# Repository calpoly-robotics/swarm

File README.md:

swarm
=====

The base will, every so often, poll every address on the bus to see who is there.
We may have it restrict to a smaller number of addresses for increased efficiency
The base will then, device by device, ask them if they have any data to offload.

TODO:
	MX25L25635EZNI-12G
	UART with base station
	base station test code
	Buzzer
	Ledtask
		blink specific led
		on for duration
	Battery task
		when voltage is <3.4V full sleep. wake every few minutes
		when voltage is <3.6V sleep. Wake every minute and be annoying
	Just ensure all hardware has code

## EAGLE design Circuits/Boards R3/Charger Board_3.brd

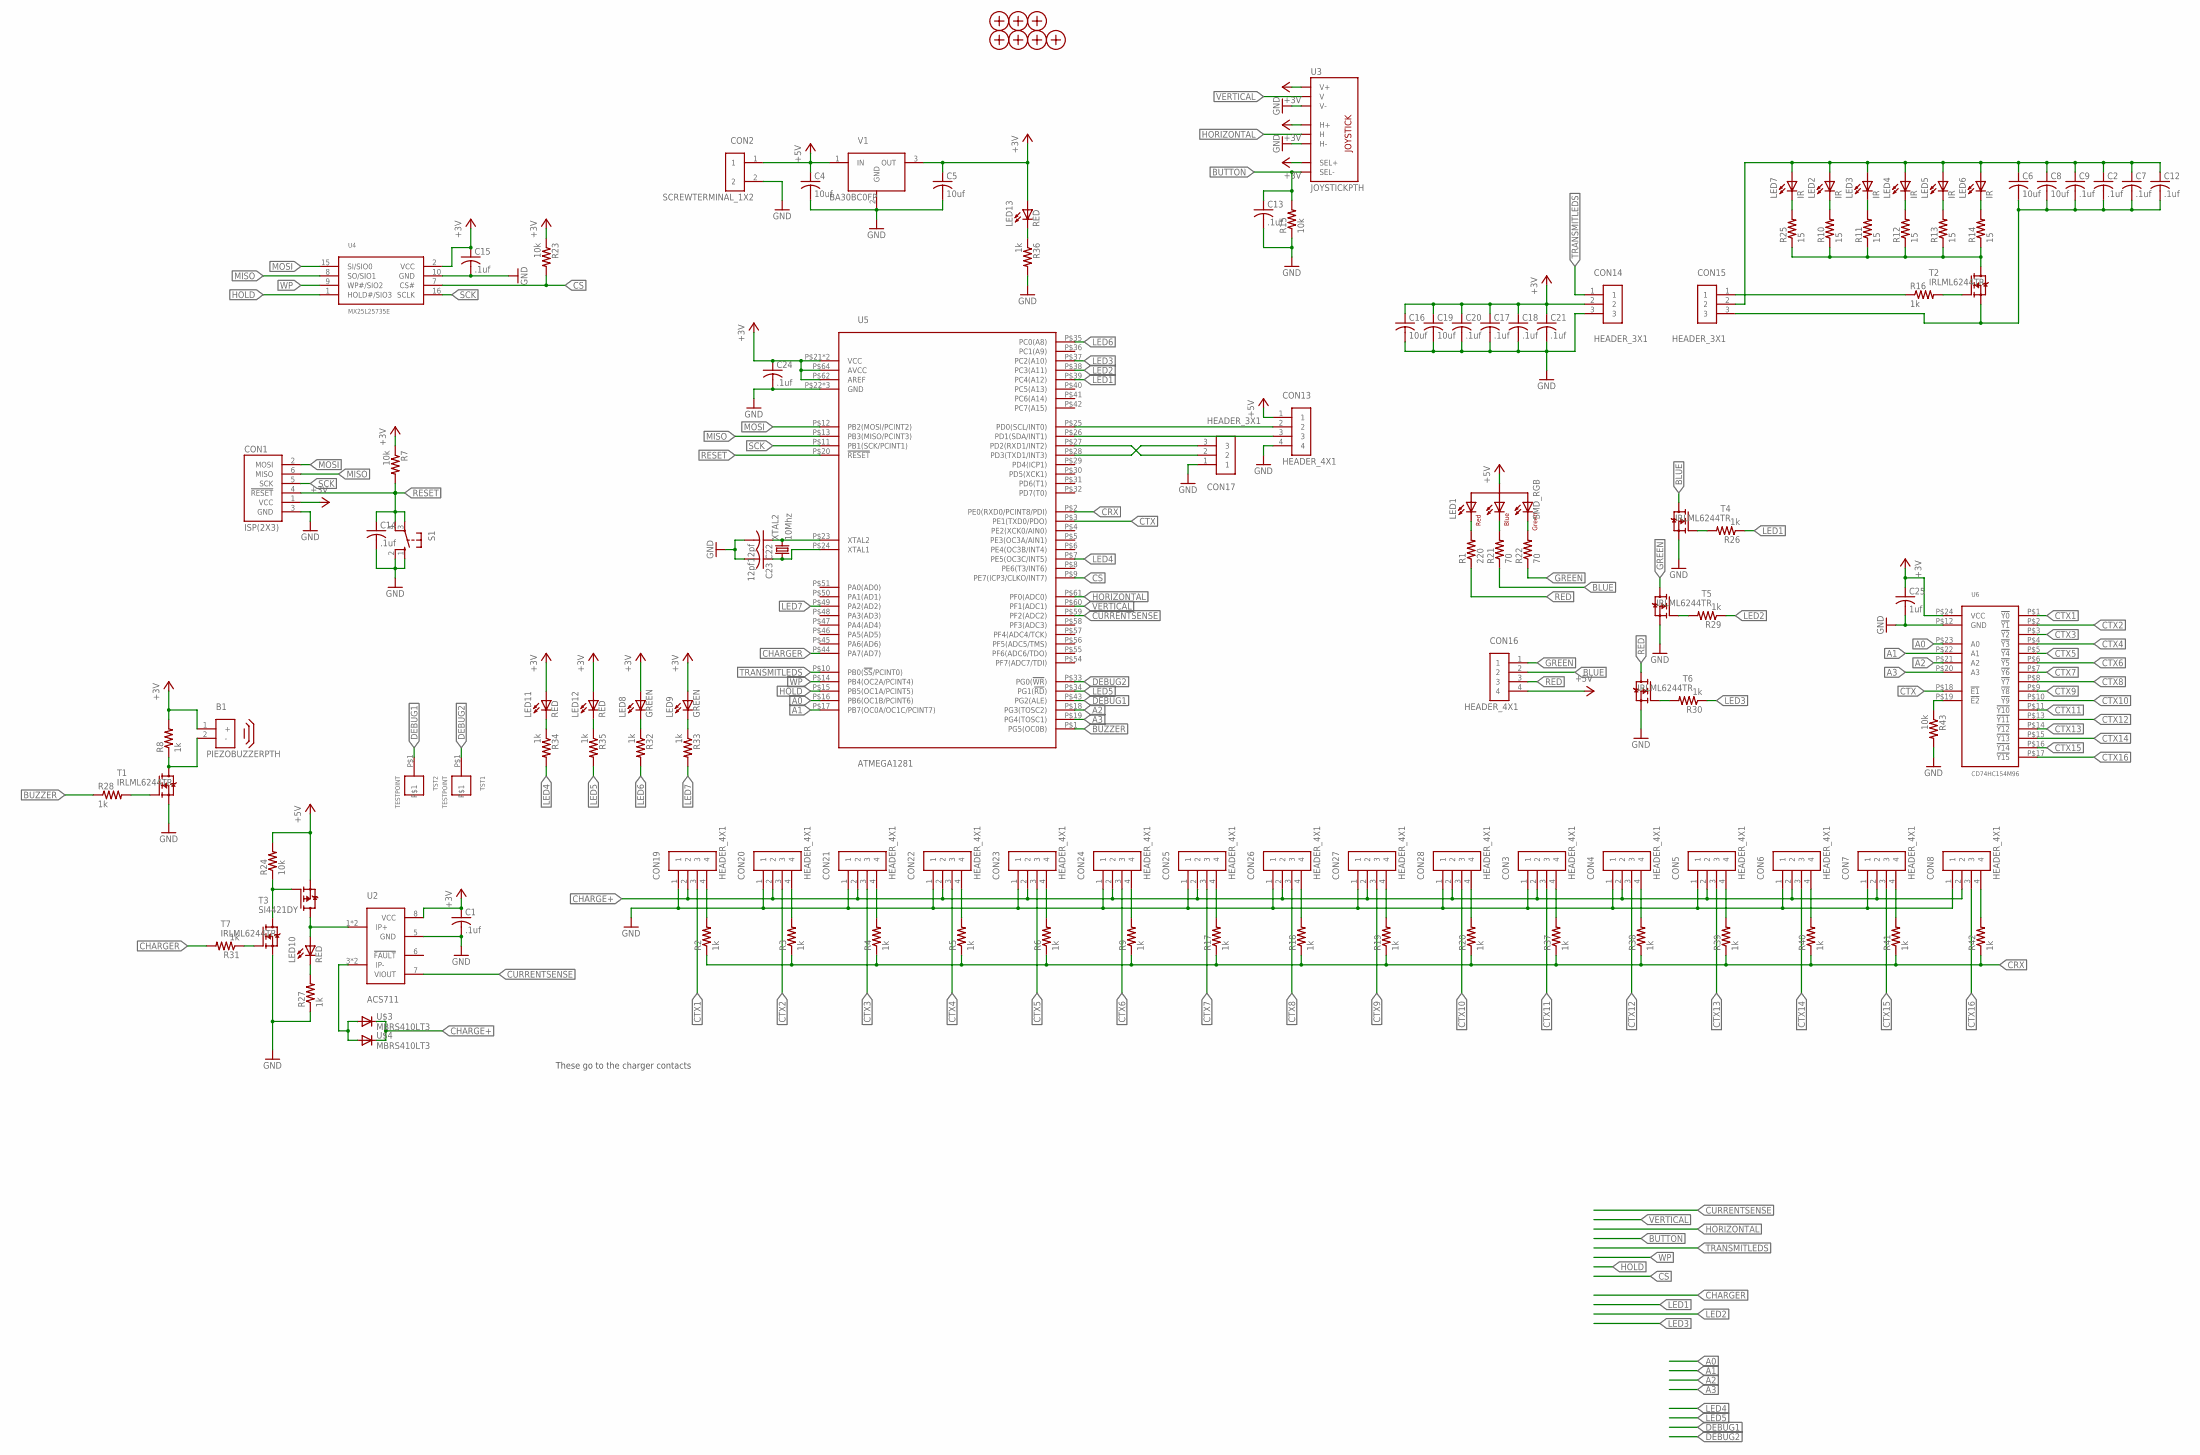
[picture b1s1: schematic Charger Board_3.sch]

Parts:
B1: PIEZOBUZZERPTH; PIEZOBUZZER
C1, C2, C7, C9, C12, C13, C14, C15, C17, C18, C20, C21, C24: .1uf; 0603
C4, C5, C6, C8, C16, C19: 10uf; 0805
C22, C23: 12pf; 0603
C25: 1uf; 0603
CON1: ISP(2X3); PINHEADER(2X3)
CON2: SCREWTERMINAL_1X2
CON3, CON4, CON5, CON6, CON7, CON8, CON13, CON16, CON19, CON20, CON21, CON22, CON23, CON24, CON25, CON26, CON27, CON28: HEADER_4X1; 4PINHEADER_.100"
CON14, CON15, CON17: HEADER_3X1; 3PINHEADER_.100"
H1, H2, H3, H4, H5, H6, H7: MOUNTINGHOLE
LED1: SMD_RGB; PLCC4
LED2, LED3, LED4, LED5, LED6, LED7: IR; 5MM_LED_RA
LED8, LED9: GREEN; LED0603
LED10, LED11, LED12, LED13: RED; LED0603
R1: 220; 0603
R2, R3, R4, R5, R6, R8, R9, R16, R17, R18, R19, R20, R26, R27, R28, R29, R30, R31, R32, R33, R34, R35, R36, R37, R38, R39, R40, R41, R42: 1k; 0603
R7, R15, R23, R24, R43: 10k; 0603
R10, R11, R12, R13, R14, R25: 15; 0603
R21, R22: 70; 0603
S1: 10-XX; B3F-10XX
T1, T2, T4, T5, T6, T7: IRLML6244TR; SOT23
T3: SI4421DY; S0-8
TST1, TST2: TESTPOINT
U2: ACS711; 8SOIC
U3: JOYSTICKPTH; JOYSTICK
U4: MX25L25735E; SOIC16R
U5: ATMEGA1281; TQFP64
U6: CD74HC154M96; 24SOIC
U$3, U$4: MBRS410LT3; SMD_DIODE
V1: BA30BC0FP; DPAK
XTAL2: 10Mhz; SMDXTAL

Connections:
+3V: B1.1 (+), C1.1, C5.1, C15.1, C16.1, C17.1, C18.1, C19.1, C20.1, C21.1, C24.1, C25.1, CON1.1 (VCC), CON14.2, LED8.2 (A), LED9.2 (A), LED11.2 (A), LED12.2 (A), LED13.2 (A), R7.1, R8.2, R23.1, U2.8 (VCC), U3.B1A (SEL+), U3.H1 (H+), U3.V1 (V+), U4.2 (VCC), U5.P$21 (VCC), U5.P$52 (VCC), U5.P$62 (AREF), U5.P$64 (AVCC), U6.P$24 (VCC), V1.3 (OUT)
+5V: C4.1, CON2.1, CON13.1, CON16.4, LED1.2 (COMMONANODE), R24.2, T3.1 (S), T3.2 (S), T3.3 (S), V1.1 (IN)
A0: U5.P$16 (PB6(OC1B/PCINT6)), U6.P$23 (A0)
A1: U5.P$17 (PB7(OC0A/OC1C/PCINT7)), U6.P$22 (A1)
A2: U5.P$18 (PG3(TOSC2)), U6.P$21 (A2)
A3: U5.P$19 (PG4(TOSC1)), U6.P$20 (A3)
BLUE: CON16.2, R21.1, T4.3 (D)
BUTTON: C13.1, R15.2, U3.B2A (SEL-)
BUZZER: R28.1, U5.P$1 (PG5(OC0B))
CHARGE+: CON3.2, CON4.2, CON5.2, CON6.2, CON7.2, CON8.2, CON19.2, CON20.2, CON21.2, CON22.2, CON23.2, CON24.2, CON25.2, CON26.2, CON27.2, CON28.2, U$3.2 (C), U$4.2 (C)
CHARGER: R31.2, U5.P$44 (PA7(AD7))
CRX: R2.1, R3.1, R4.1, R5.1, R6.1, R9.1, R17.1, R18.1, R19.1, R20.1, R37.1, R38.1, R39.1, R40.1, R41.1, R42.1, U5.P$2 (PE0(RXD0/PCINT8/PDI))
CS: R23.2, U4.7 (CS#), U5.P$9 (PE7(ICP3/CLKO/INT7))
CTX: U5.P$3 (PE1(TXD0/PDO)), U6.P$18 (!E1)
CTX1: CON19.3, U6.P$1 (!Y0)
CTX2: CON20.3, U6.P$2 (!Y1)
CTX3: CON21.3, U6.P$3 (!Y2)
CTX4: CON22.3, U6.P$4 (!Y3)
CTX5: CON23.3, U6.P$5 (!Y4)
CTX6: CON24.3, U6.P$6 (!Y5)
CTX7: CON25.3, U6.P$7 (!Y6)
CTX8: CON26.3, U6.P$8 (!Y7)
CTX9: CON27.3, U6.P$9 (!Y8)
CTX10: CON28.3, U6.P$10 (!Y9)
CTX11: CON3.3, U6.P$11 (!Y10)
CTX12: CON4.3, U6.P$13 (!Y11)
CTX13: CON5.3, U6.P$14 (!Y12)
CTX14: CON6.3, U6.P$15 (!Y13)
CTX15: CON7.3, U6.P$16 (!Y14)
CTX16: CON8.3, U6.P$17 (!Y15)
CURRENTSENSE: U2.7 (VIOUT), U5.P$59 (PF2(ADC2))
DEBUG1: TST2.P$1, U5.P$43 (PG2(ALE))
DEBUG2: TST1.P$1, U5.P$33 (PG0(!WR!))
GND: C1.2, C4.2, C5.2, C13.2, C14.2, C15.2, C16.2, C17.2, C18.2, C19.2, C20.2, C21.2, C22.2, C23.2, C24.2, C25.2, CON1.3 (GND), CON2.2, CON3.1, CON4.1, CON5.1, CON6.1, CON7.1, CON8.1, CON13.4, CON14.3, CON17.1, CON19.1, CON20.1, CON21.1, CON22.1, CON23.1, CON24.1, CON25.1, CON26.1, CON27.1, CON28.1, R15.1, R27.1, R36.2, R43.2, S1.1 (S), S1.2 (S1), T1.2 (S), T4.2 (S), T5.2 (S), T6.2 (S), T7.2 (S), U2.5 (GND), U3.H3 (H-), U3.V3 (V-), U4.10 (GND), U5.P$22 (GND), U5.P$53 (GND), U5.P$63 (GND), U6.P$12 (GND), V1.2 (GND)
GREEN: CON16.1, R22.1, T5.3 (D)
HOLD: U4.1 (HOLD#/SIO3), U5.P$15 (PB5(OC1A/PCINT5))
HORIZONTAL: U3.H2 (H), U5.P$61 (PF0(ADC0))
LED1: R26.1, U5.P$39 (PC4(A12))
LED2: R29.1, U5.P$38 (PC3(A11))
LED3: R30.1, U5.P$37 (PC2(A10))
LED4: R34.2, U5.P$7 (PE5(OC3C/INT5))
LED5: R35.2, U5.P$34 (PG1(!RD!))
LED6: R32.2, U5.P$35 (PC0(A8))
LED7: R33.2, U5.P$49 (PA2(AD2))
MISO: CON1.6 (MISO), U4.8 (SO/SIO1), U5.P$13 (PB3(MISO/PCINT3))
MOSI: CON1.2 (MOSI), U4.15 (SI/SIO0), U5.P$12 (PB2(MOSI/PCINT2))
unnamed: LED10.2 (A), T3.5 (D), T3.6 (D), T3.7 (D), T3.8 (D), U2.1 (IP+), U2.2 (IP+)
unnamed: CON15.1, R16.1
unnamed: C2.1, C6.1, C7.1, C8.1, C9.1, C12.1, CON15.2, LED2.1 (A), LED3.1 (A), LED4.1 (A), LED5.1 (A), LED6.1 (A), LED7.1 (A)
unnamed: C2.2, C6.2, C7.2, C8.2, C9.2, C12.2, CON15.3, T2.2 (S)
unnamed: LED7.2 (C), R25.2
unnamed: B1.2 (-), R8.1, T1.3 (D)
unnamed: R10.1, R11.1, R12.1, R13.1, R14.1, R25.1, T2.3 (D)
unnamed: R16.2, T2.1 (G)
unnamed: LED2.2 (C), R10.2
unnamed: LED3.2 (C), R11.2
unnamed: LED4.2 (C), R12.2
unnamed: LED5.2 (C), R13.2
unnamed: LED6.2 (C), R14.2
unnamed: R24.1, T3.4 (G), T7.3 (D)
unnamed: R31.1, T7.1 (G)
unnamed: LED10.1 (C), R27.2
unnamed: U2.3 (IP-), U2.4 (IP-), U$3.1 (A), U$4.1 (A)
unnamed: CON20.4, R3.2
unnamed: R28.2, T1.1 (G)
unnamed: CON19.4, R2.2
unnamed: CON21.4, R4.2
unnamed: CON22.4, R5.2
unnamed: CON23.4, R6.2
unnamed: CON24.4, R9.2
unnamed: CON25.4, R17.2
unnamed: CON26.4, R18.2
unnamed: CON27.4, R19.2
unnamed: CON28.4, R20.2
unnamed: R26.2, T4.1 (G)
unnamed: LED1.1 (REDCATHODE), R1.2
unnamed: LED1.3 (BLUECATHODE), R21.2
unnamed: LED1.4 (GREENCATHODE), R22.2
unnamed: R29.2, T5.1 (G)
unnamed: R30.2, T6.1 (G)
unnamed: LED8.1 (C), R32.1
unnamed: LED9.1 (C), R33.1
unnamed: LED11.1 (C), R34.1
unnamed: LED12.1 (C), R35.1
unnamed: LED13.1 (C), R36.1
unnamed: C22.1, U5.P$23 (XTAL2), XTAL2.2
unnamed: C23.1, U5.P$24 (XTAL1), XTAL2.1
unnamed: CON3.4, R37.2
unnamed: CON4.4, R38.2
unnamed: CON5.4, R39.2
unnamed: CON6.4, R40.2
unnamed: CON7.4, R41.2
unnamed: CON8.4, R42.2
unnamed: CON13.2, U5.P$25 (PD0(SCL/INT0))
unnamed: CON13.3, U5.P$26 (PD1(SDA/INT1))
unnamed: R43.1, U6.P$19 (!E2)
unnamed: CON17.2, U5.P$27 (PD2(RXD1/INT2))
unnamed: CON17.3, U5.P$28 (PD3(TXD1/INT3))
RED: CON16.3, R1.1, T6.3 (D)
RESET: C14.1, CON1.4 (!RESET), R7.2, S1.3, S1.4 (P1), U5.P$20 (!RESET!)
SCK: CON1.5 (SCK), U4.16 (SCLK), U5.P$11 (PB1(SCK/PCINT1))
TRANSMITLEDS: CON14.1, U5.P$10 (PB0(!SS!/PCINT0))
VERTICAL: U3.V2 (V), U5.P$60 (PF1(ADC1))
WP: U4.9 (WP#/SIO2), U5.P$14 (PB4(OC2A/PCINT4))

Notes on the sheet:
These go to the charger contacts

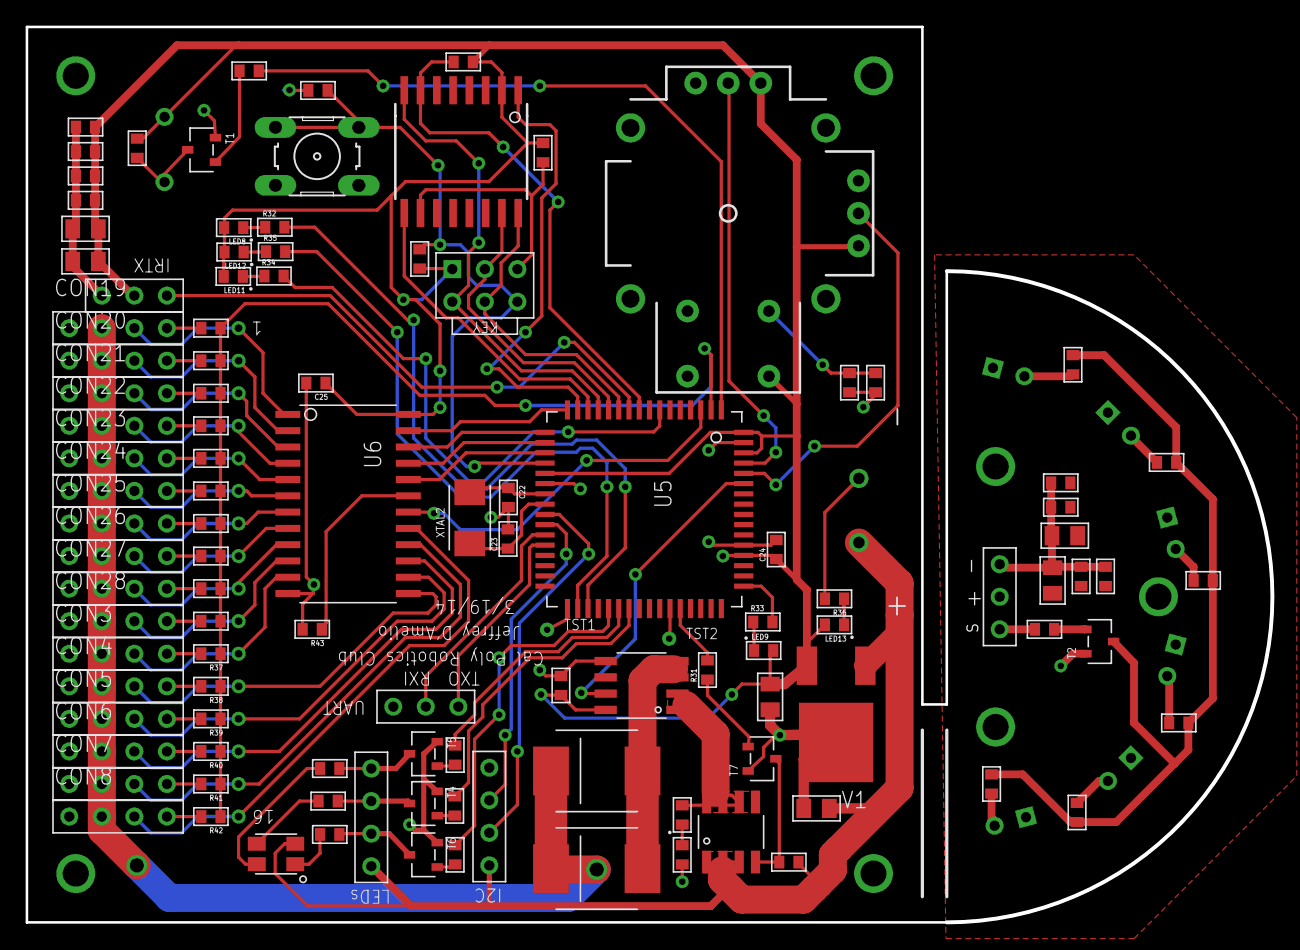
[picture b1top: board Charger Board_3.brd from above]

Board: 2 copper layers, 97.2 x 69.8 mm, 128 parts (0 on the bottom side), 104 nets.

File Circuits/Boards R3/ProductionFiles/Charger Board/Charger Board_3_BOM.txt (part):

Partlist exported from C:/Users/Jeffrey/Documents/GitHub/swarm/Circuits/Boards R3/Charger Board_3.sch at 3/21/2014 3:27:56 AM

Qty Value             Device                Package           Parts                                                                                                                                    Description                                        MF MPN      OC_FARNELL OC_NEWARK
1                     10-XX                 B3F-10XX          S1                                                                                                                                       OMRON SWITCH                                          B3F-1000 176432     36M3542  
13  .1uf              CAP0603               0603              C1, C2, C7, C9, C12, C13, C14, C15, C17, C18, C20, C21, C24                                                                                                                                                                 
1   10Mhz             NX5032GA-10.000000MHZ SMDXTAL           XTAL2                                                                                                                                    Digikey Part Number: 644-1033-1-ND                                                 
5   10k               RES0603               0603              R7, R15, R23, R24, R43                                                                                                                                                                                                      
6   10uf              CAP0805               0805              C4, C5, C6, C8, C16, C19                                                                                                                                                                                                    
2   12pf              CAP0603               0603              C22, C23                                                                                                                                                                                                                    
6   15                RES0603               0603              R10, R11, R12, R13, R14, R25                                                                                                                                                                                                
29  1k                RES0603               0603              R2, R3, R4, R5, R6, R8, R9, R16, R17, R18, R19, R20, R26, R27, R28, R29, R30, R31, R32, R33, R34, R35, R36, R37, R38, R39, R40, R41, R42                                                                                    
1   1uf               CAP0603               0603              C25                                                                                                                                                                                                                         
1   220               RES0603               0603              R1                                                                                                                                                                                                                          
2   70                RES0603               0603              R21, R22                                                                                                                                                                                                                    
1   ACS711            ACS711                8SOIC             U2                                                                                                                                                                                                                          
1   ATMEGA1281        ATMEGA1281            TQFP64            U5                                                                                                                                       Digikey Part Number: ATMEGA1281V-8AU-ND                                            
1   BA30BC0FP         BA30BC0FP             DPAK              V1                                                                                                                                       Digikey Part Number: BA30BC0FP-E2CT-ND                                             
1   CD74HC154M96      CD74HC154M96          24SOIC            U6                                                                                                                                       Digikey Part Number: 296-24352-1-ND                                                
2   GREEN             LED0603               LED0603           LED8, LED9                                                                                                                                                                                                                  
3   HEADER_3X1        HEADER_3X1            3PINHEADER_.100"  CON14, CON15, CON17                                                                                                                                                                                                         
18  HEADER_4X1        HEADER_4X1            4PINHEADER_.100"  CON3, CON4, CON5, CON6, CON7, CON8, CON13, CON16, CON19, CON20, CON21, CON22, CON23, CON24, CON25, CON26, CON27, CON28                                                                                                      
6   IR                LED5MMRA              5MM_LED_RA        LED2, LED3, LED4, LED5, LED6, LED7                                                                                                                                                                                          
6   IRLML6244TR       IRLML6244TR           SOT23             T1, T2, T4, T5, T6, T7                                                                                                                   Digikey Part Number: IRLML6244TRPBFCT-ND                                           
1   ISP(2X3)          ISP(2X3)              PINHEADER(2X3)    CON1                                                                                                                                                                                                                        
1   JOYSTICKPTH       JOYSTICKPTH           JOYSTICK          U3                                                                                                                                       Thumb Joystick                                                                     
2   MBRS410LT3        MBRS410LT3            SMD_DIODE         U$3, U$4                                                                                                                                 Digikey Part Number: MBRS410LT3GOSCT-ND                                            
7   MOUNTINGHOLE      MOUNTINGHOLE          MOUNTINGHOLE      H1, H2, H3, H4, H5, H6, H7                                                                                                                                                                                                  
1   MX25L25735E       MX25L25735E           SOIC16R           U4                                                                                                                                       Digikey Part Number: 1092-1000-ND                                                  
1   PIEZOBUZZERPTH    PIEZOBUZZERPTH        PIEZOBUZZER       B1                                                                                                                                       Digikey Part Number: 445-2525-1-ND                                                 
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
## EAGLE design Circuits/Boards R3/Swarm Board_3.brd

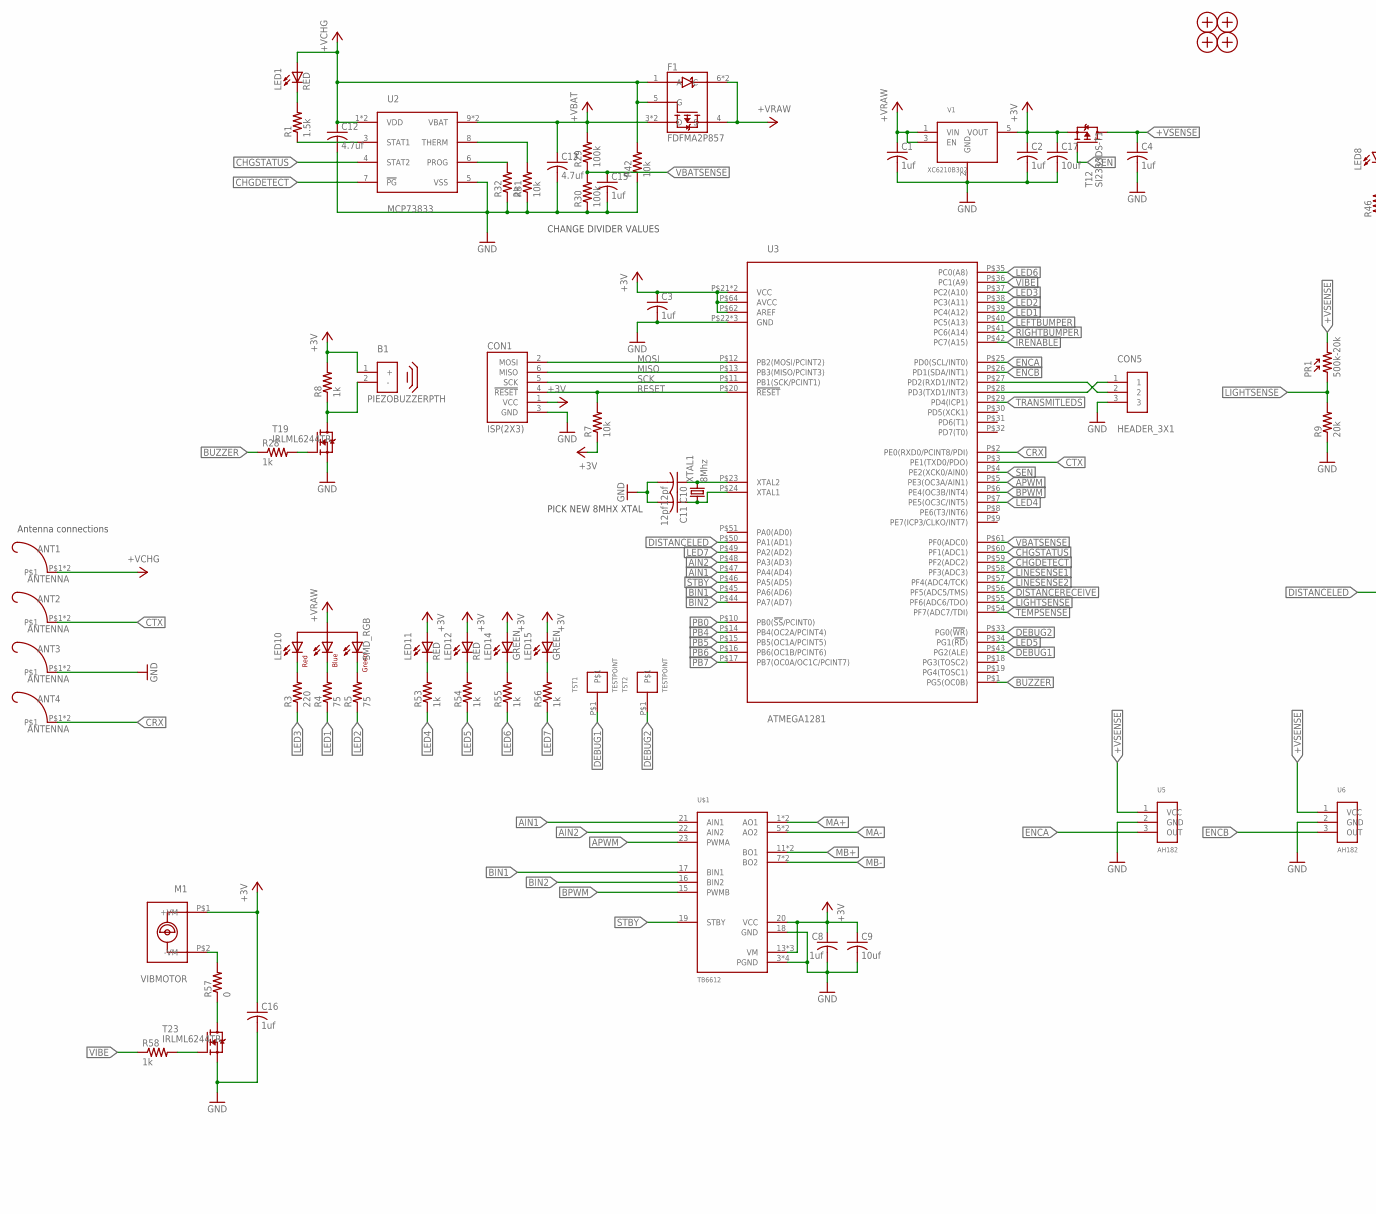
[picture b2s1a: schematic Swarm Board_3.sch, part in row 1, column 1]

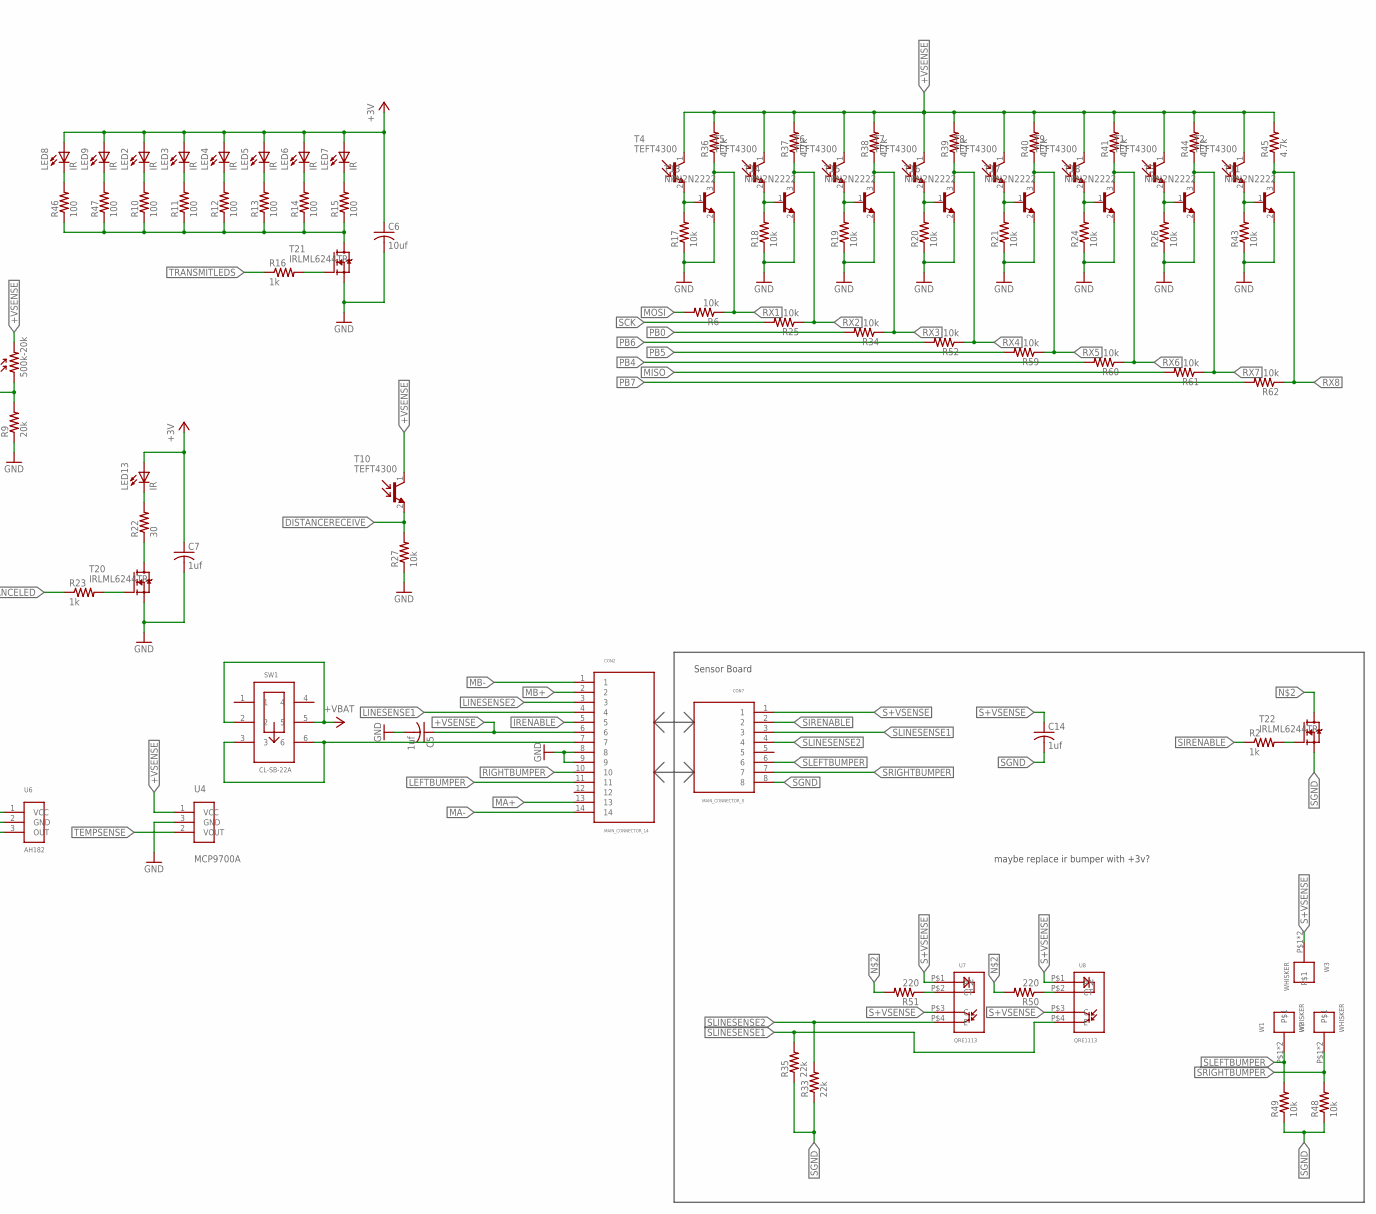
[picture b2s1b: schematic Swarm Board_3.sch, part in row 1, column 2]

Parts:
ANT1, ANT2, ANT3, ANT4: ANTENNA
B1: PIEZOBUZZERPTH; PIEZOBUZZER
C1, C2, C3, C4, C5, C7, C8, C14, C15, C16: 1uf; 0603
C6, C9, C17: 10uf; 0805
C10, C11: 12pf; 0603
C12, C13: 4.7uf; 0603
CON1: ISP(2X3); PINHEADER(2X3)
CON2: MAIN_CONNECTOR_14; FEMALE_HEADER_2MM_2X7_SMD
CON5: HEADER_3X1; 3PINHEADER_.100"
CON7: MAIN_CONNECTOR_8; FEMALE_HEADER_2MM_2X4
F1: FDFMA2P857; MICROFET2X2MM
H1, H2, H3, H4: MOUNTINGHOLE
LED1, LED11, LED12: RED; LED0603
LED2, LED3, LED4, LED5, LED6, LED7, LED8, LED9, LED13: IR; 5MM_LED_RA
LED10: SMD_RGB; PLCC4
LED14, LED15: GREEN; LED0603
M1: VIBMOTOR
PR1: 500k-20k; CDSPHOTOCELL
R1: 1.5k; 0603
R2, R8, R16, R23, R28, R53, R54, R55, R56, R58: 1k; 0603
R3, R50, R51: 220; 0603
R4, R5: 75; 0603
R6, R7, R17, R18, R19, R20, R21, R24, R25, R26, R27, R31, R34, R42, R43, R48, R49, R52, R59, R60, R61, R62: 10k; 0603
R9: 20k; 0603
R10, R11, R12, R13, R14, R15, R46, R47: 100; 0603
R22: 30; 0603
R29, R30: 100k; 0603
R32: 2k; 0603
R33, R35: 22k; 0603
R36, R37, R38, R39, R40, R41, R44, R45: 4.7k; 0603
R57: 0; 0603
SW1: CL-SB-22A; CL-SB-22A-01T
T1, T2, T4, T5, T6, T7, T8, T9, T10: TEFT4300; 3MM_LED_RA
T3, T11, T13, T14, T15, T16, T17, T18: NPN2N2222; SOT23
T12: SI2333DS-T1; SOT23
T19, T20, T21, T22, T23: IRLML6244TR; SOT23
TST1, TST2: TESTPOINT
U2: MCP73833; MSOP10
U3: ATMEGA1281; TQFP64
U4: MCP9700A; SOT23
U5, U6: AH182; 3PINHEADER_.100"
U7, U8: QRE1113
U$1: TB6612; 24SSOP
V1: XC6210B302; (OT)SOT-23(5PAD)
W1, W2, W3: WHISKER
XTAL1: 8Mhz; SMDXTAL

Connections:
+3V: B1.1 (+), C2.1, C3.1, C6.1, C7.1, C8.1, C9.1, C16.1, C17.1, CON1.1 (VCC), LED2.1 (A), LED3.1 (A), LED4.1 (A), LED5.1 (A), LED6.1 (A), LED7.1 (A), LED8.1 (A), LED9.1 (A), LED11.2 (A), LED12.2 (A), LED13.1 (A), LED14.2 (A), LED15.2 (A), M1.P$1 (+VM), R7.1, R8.2, T12.2 (S), U3.P$21 (VCC), U3.P$52 (VCC), U3.P$62 (AREF), U3.P$64 (AVCC), U$1.13 (VM), U$1.14 (VM), U$1.20 (VCC), U$1.24 (VM), V1.5 (VOUT)
+VBAT: C13.1, F1.3 (D), F1.8 (D), R29.2, SW1.2, SW1.5, U2.9 (VBAT), U2.10 (VBAT)
+VCHG: ANT1.P$1, ANT1.P$2, C12.1, F1.1 (A), F1.5 (G), LED1.2 (A), R42.2, U2.1 (VDD), U2.2 (VDD)
+VRAW: C1.1, F1.4 (S), F1.6 (C), F1.7 (C), LED10.2 (COMMONANODE), V1.1 (VIN), V1.3 (EN)
+VSENSE: C4.1, C5.1, CON2.6, PR1.2, R36.2, R37.2, R38.2, R39.2, R40.2, R41.2, R44.2, R45.2, T1.1 (C), T2.1 (C), T4.1 (C), T5.1 (C), T6.1 (C), T7.1 (C), T8.1 (C), T9.1 (C), T10.1 (C), T12.3 (D), U4.1 (VCC), U5.1 (VCC), U6.1 (VCC)
AIN1: U3.P$47 (PA4(AD4)), U$1.21 (AIN1)
AIN2: U3.P$48 (PA3(AD3)), U$1.22 (AIN2)
APWM: U3.P$5 (PE3(OC3A/AIN1)), U$1.23 (PWMA)
BIN1: U3.P$45 (PA6(AD6)), U$1.17 (BIN1)
BIN2: U3.P$44 (PA7(AD7)), U$1.16 (BIN2)
BPWM: U3.P$6 (PE4(OC3B/INT4)), U$1.15 (PWMB)
BUZZER: R28.1, U3.P$1 (PG5(OC0B))
CHGDETECT: U2.7 (!PG), U3.P$59 (PF2(ADC2))
CHGSTATUS: U2.4 (STAT2), U3.P$60 (PF1(ADC1))
CRX: ANT4.P$1, ANT4.P$2, U3.P$2 (PE0(RXD0/PCINT8/PDI))
CTX: ANT2.P$1, ANT2.P$2, U3.P$3 (PE1(TXD0/PDO))
DATAANTENNA: CON5.1, U3.P$28 (PD3(TXD1/INT3))
DEBUG1: TST1.P$1, U3.P$43 (PG2(ALE))
DEBUG2: TST2.P$1, U3.P$33 (PG0(!WR!))
DISTANCELED: R23.1, U3.P$50 (PA1(AD1))
DISTANCERECEIVE: R27.2, T10.2 (E), U3.P$56 (PF5(ADC5/TMS))
ENCA: U3.P$25 (PD0(SCL/INT0)), U5.3 (OUT)
ENCB: U3.P$26 (PD1(SDA/INT1)), U6.3 (OUT)
GND: ANT3.P$1, ANT3.P$2, C1.2, C2.2, C3.2, C4.2, C5.2, C6.2, C7.2, C8.2, C9.2, C10.2, C11.2, C12.2, C13.2, C15.2, C16.2, C17.2, CON1.3 (GND), CON2.8, CON2.9, CON5.3, R9.1, R17.1, R18.1, R19.1, R20.1, R21.1, R24.1, R26.1, R27.1, R30.1, R31.1, R32.1, R42.1, R43.1, T3.2 (E), T11.2 (E), T13.2 (E), T14.2 (E), T15.2 (E), T16.2 (E), T17.2 (E), T18.2 (E), T19.2 (S), T20.2 (S), T21.2 (S), T23.2 (S), U2.5 (VSS), U3.P$22 (GND), U3.P$53 (GND), U3.P$63 (GND), U4.3 (GND), U5.2 (GND), U6.2 (GND), U$1.3 (PGND), U$1.4 (PGND), U$1.9 (PGND), U$1.10 (PGND), U$1.18 (GND), V1.2 (GND)
IRENABLE: CON2.5, U3.P$42 (PC7(A15))
LED1: R4.1, U3.P$39 (PC4(A12))
LED2: R5.1, U3.P$38 (PC3(A11))
LED3: R3.1, U3.P$37 (PC2(A10))
LED4: R53.1, U3.P$7 (PE5(OC3C/INT5))
LED5: R54.1, U3.P$34 (PG1(!RD!))
LED6: R55.1, U3.P$35 (PC0(A8))
LED7: R56.1, U3.P$49 (PA2(AD2))
LEFTBUMPER: CON2.11, U3.P$40 (PC5(A13))
LIGHTSENSE: PR1.1, R9.2, U3.P$55 (PF6(ADC6/TDO))
LINESENSE1: CON2.4, U3.P$58 (PF3(ADC3))
LINESENSE2: CON2.3, U3.P$57 (PF4(ADC4/TCK))
MA+: CON2.13, U$1.1 (AO1), U$1.2 (AO1)
MA-: CON2.14, U$1.5 (AO2), U$1.6 (AO2)
MB+: CON2.2, U$1.11 (BO1), U$1.12 (BO1)
MB-: CON2.1, U$1.7 (BO2), U$1.8 (BO2)
MISO: CON1.6 (MISO), R61.2, U3.P$13 (PB3(MISO/PCINT3))
MOSI: CON1.2 (MOSI), R6.2, U3.P$12 (PB2(MOSI/PCINT2))
unnamed: LED1.1 (C), R1.2
unnamed: R50.2, R51.2, T22.3 (D)
unnamed: R43.2, T2.2 (E), T11.1 (B)
unnamed: R2.2, T22.1 (G)
unnamed: CON2.7, SW1.3, SW1.6
unnamed: R26.2, T1.2 (E), T3.1 (B)
unnamed: R57.1, T23.3 (D)
unnamed: CON5.2, U3.P$27 (PD2(RXD1/INT2))
unnamed: B1.2 (-), R8.1, T19.3 (D)
unnamed: R10.1, R11.1, R12.1, R13.1, R14.1, R15.1, R46.1, R47.1, T21.3 (D)
unnamed: R16.2, T21.1 (G)
unnamed: R22.1, T20.3 (D)
unnamed: LED2.2 (C), R10.2
unnamed: LED3.2 (C), R11.2
unnamed: LED4.2 (C), R12.2
unnamed: LED5.2 (C), R13.2
unnamed: LED6.2 (C), R14.2
unnamed: LED7.2 (C), R15.2
unnamed: R23.2, T20.1 (G)
unnamed: LED8.2 (C), R46.2
unnamed: LED9.2 (C), R47.2
unnamed: R31.2, U2.8 (THERM)
unnamed: C10.1, U3.P$23 (XTAL2), XTAL1.2
unnamed: C11.1, U3.P$24 (XTAL1), XTAL1.1
unnamed: LED13.2 (C), R22.2
unnamed: R28.2, T19.1 (G)
unnamed: R17.2, T4.2 (E), T13.1 (B)
unnamed: R32.2, U2.6 (PROG)
unnamed: R51.1, U7.P$2 (CT)
unnamed: LED10.1 (REDCATHODE), R3.2
unnamed: LED10.3 (BLUECATHODE), R4.2
unnamed: LED10.4 (GREENCATHODE), R5.2
unnamed: R1.1, U2.3 (STAT1)
unnamed: R24.2, T9.2 (E), T18.1 (B)
unnamed: R21.2, T8.2 (E), T17.1 (B)
unnamed: R20.2, T7.2 (E), T16.1 (B)
unnamed: R19.2, T6.2 (E), T15.1 (B)
unnamed: R18.2, T5.2 (E), T14.1 (B)
unnamed: R50.1, U8.P$2 (CT)
unnamed: LED11.1 (C), R53.2
unnamed: R58.2, T23.1 (G)
unnamed: LED12.1 (C), R54.2
unnamed: LED14.1 (C), R55.2
unnamed: LED15.1 (C), R56.2
unnamed: M1.P$2 (-VM), R57.2
PB0: R34.2, U3.P$10 (PB0(!SS!/PCINT0))
PB4: R60.2, U3.P$14 (PB4(OC2A/PCINT4))
PB5: R59.2, U3.P$15 (PB5(OC1A/PCINT5))
PB6: R52.2, U3.P$16 (PB6(OC1B/PCINT6))
PB7: R62.2, U3.P$17 (PB7(OC0A/OC1C/PCINT7))
RESET: CON1.4 (!RESET), R7.2, U3.P$20 (!RESET!)
RIGHTBUMPER: CON2.10, U3.P$41 (PC6(A14))
RX1: R6.1, R36.1, T13.3 (C)
RX2: R25.1, R37.1, T14.3 (C)
RX3: R34.1, R38.1, T15.3 (C)
RX4: R39.1, R52.1, T16.3 (C)
RX5: R40.1, R59.1, T17.3 (C)
RX6: R41.1, R60.1, T18.3 (C)
RX7: R44.1, R61.1, T3.3 (C)
RX8: R45.1, R62.1, T11.3 (C)
S+VSENSE: C14.1, CON7.1, U7.P$1 (AN), U7.P$3 (C), U8.P$1 (AN), U8.P$3 (C), W3.P$1, W3.P$2
SCK: CON1.5 (SCK), R25.2, U3.P$11 (PB1(SCK/PCINT1))
SEN: T12.1 (G), U3.P$4 (PE2(XCK0/AIN0))
SGND: C14.2, CON7.8, R33.1, R35.1, R48.1, R49.1, T22.2 (S)
SIRENABLE: CON7.2, R2.1
SLEFTBUMPER: CON7.6, R49.2, W1.P$1, W1.P$2
SLINESENSE1: CON7.3, R35.2, U8.P$4 (E)
SLINESENSE2: CON7.4, R33.2, U7.P$4 (E)
SRIGHTBUMPER: CON7.7, R48.2, W2.P$1, W2.P$2
STBY: U3.P$46 (PA5(AD5)), U$1.19 (STBY)
TEMPSENSE: U3.P$54 (PF7(ADC7/TDI)), U4.2 (VOUT)
TRANSMITLEDS: R16.1, U3.P$29 (PD4(ICP1))
VBATSENSE: C15.1, R29.1, R30.2, U3.P$61 (PF0(ADC0))
VIBE: R58.1, U3.P$36 (PC1(A9))

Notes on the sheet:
Antenna connections
Sensor Board
PICK NEW 8MHX XTAL
CHANGE DIVIDER VALUES
maybe replace ir bumper with +3v?

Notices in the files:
parts and their libraries:
SparkFun: Licensing: CC v3.0 Share-Alike You are welcome to use this library for commercial purposes.
